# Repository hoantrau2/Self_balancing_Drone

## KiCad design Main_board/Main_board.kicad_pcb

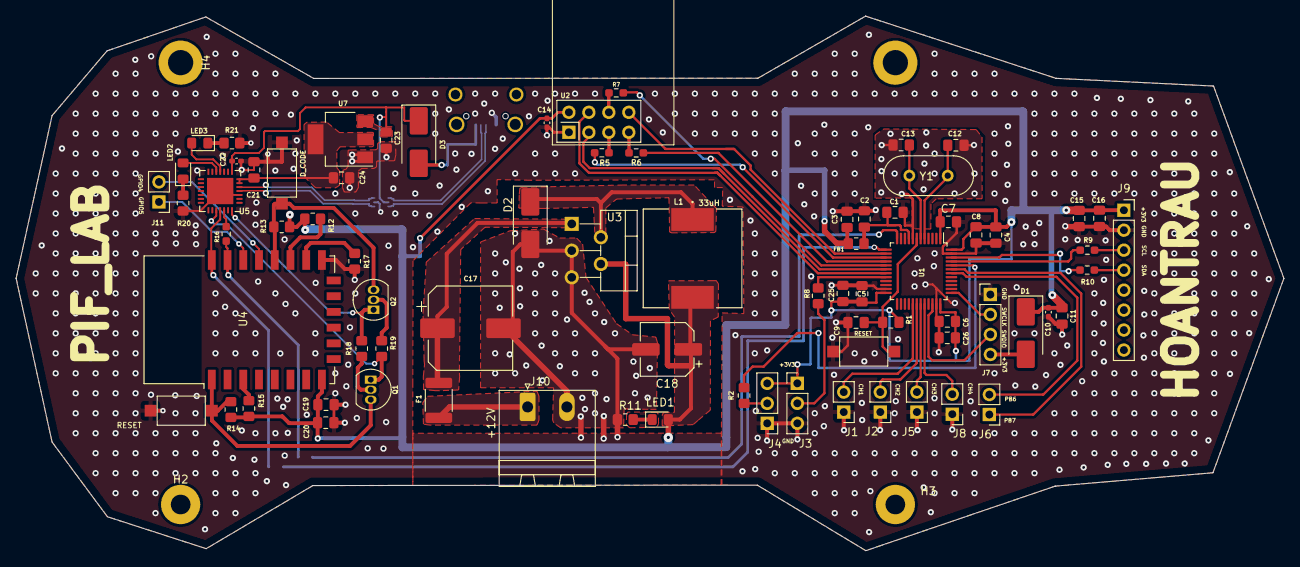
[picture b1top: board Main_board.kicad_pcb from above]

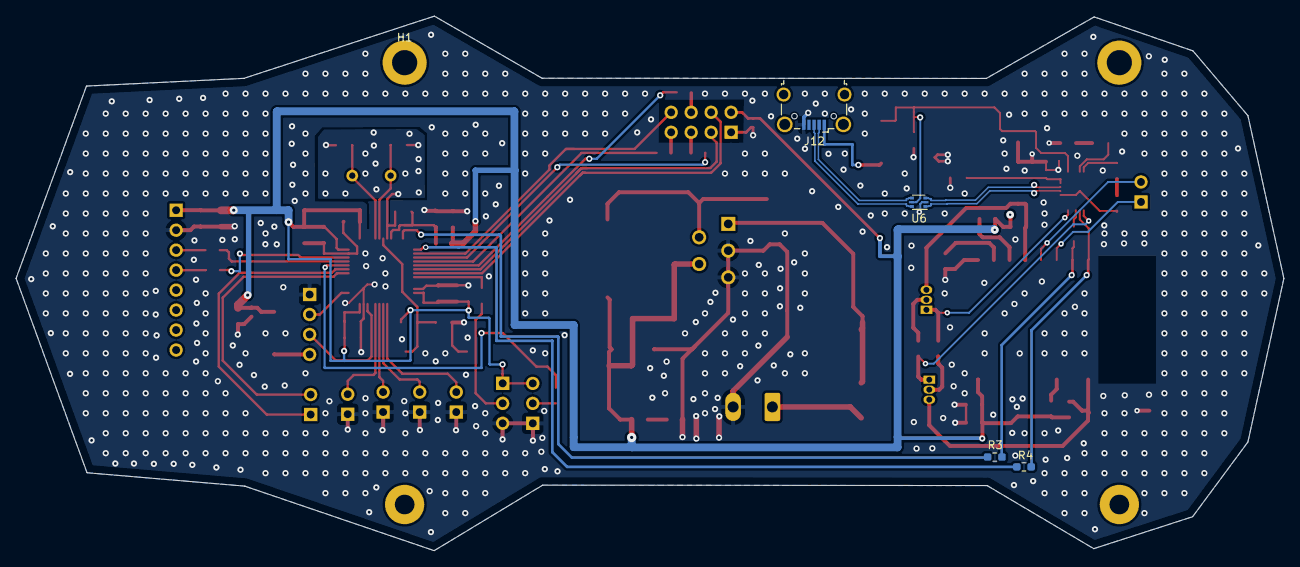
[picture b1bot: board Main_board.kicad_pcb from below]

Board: 2 copper layers, 161.2 x 68.0 mm, 85 parts (5 on the bottom side), 63 nets.

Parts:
C1: 10n; C_0805_2012Metric_Pad1.18x1.45mm_HandSolder
C2, C3: 1u; C_0805_2012Metric_Pad1.18x1.45mm_HandSolder
C4, C11, C15, C20, C23, C24, C25, C26: 10u; C_0805_2012Metric_Pad1.18x1.45mm_HandSolder
C5, C6, C7, C8, C19, C21: 100nF/50V; C_0805_2012Metric_Pad1.18x1.45mm_HandSolder
C9, C16: 100n; C_0805_2012Metric_Pad1.18x1.45mm_HandSolder
C10, C14, C22: 100nF/50V; C_0402_1005Metric_Pad0.74x0.62mm_HandSolder
C12, C13: 20p; C_0805_2012Metric_Pad1.18x1.45mm_HandSolder
C17: 680uF; CP_Elec_10x10.5
C18: 220uF; CP_Elec_6.3x7.7
D1, D2, D3: 1N5824; D_SMB_Handsoldering
D_CODE: BUTTON_GPIO0_ESP; SW_SPST_CK_RS282G05A3
F1: Fuse; Fuse_1812_4532Metric_Pad1.30x3.40mm_HandSolder
FB1: 120R; R_0805_2012Metric_Pad1.20x1.40mm_HandSolder
H1, H2, H3, H4: MountingHole; MountingHole_2.2mm_M2
J1, J2, J5, J6, J8, J11: Screw_Terminal_01x02; PinHeader_1x02_P2.54mm_Vertical
J3, J4: Screw_Terminal_01x03; PinHeader_1x03_P2.54mm_Vertical
J7: Conn_01x04_Pin; PinHeader_1x04_P2.54mm_Vertical
J9: MPU6050; PinSocket_1x08_P2.54mm_Vertical
J10: Screw_Terminal_01x02; PhoenixContact_MSTBA_2,5_2-G_1x02_P5.00mm_Horizontal
J12: USB_B_Micro; USB_Micro-B_Wuerth_629105150521_CircularHoles
L1: 33uH; IND_CDRH127_LDNP-470MC_SUM
LED1, LED2, LED3: LED; D_0805_2012Metric_Pad1.15x1.40mm_HandSolder
Q1, Q2: S8050; TO-92_Inline
R1: 10k; C_0805_2012Metric_Pad1.18x1.45mm_HandSolder
R2, R8, R13, R14, R15, R17: 10k; R_0805_2012Metric_Pad1.20x1.40mm_HandSolder
R3, R4, R5, R6, R7, R9, R10: 0; R_0603_1608Metric_Pad0.98x0.95mm_HandSolder
R11, R20, R21: 22; R_0805_2012Metric_Pad1.20x1.40mm_HandSolder
R12: 4k7; R_0805_2012Metric_Pad1.20x1.40mm_HandSolder
R16: 470; R_0603_1608Metric_Pad0.98x0.95mm_HandSolder
R18, R19: 12K; R_0805_2012Metric_Pad1.20x1.40mm_HandSolder
RESET: button_reset; SW_SPST_CK_RS282G05A3
RESET#2: Reset_button; SW_SPST_CK_RS282G05A3
U1: STM32F103C8T6; LQFP-48_7x7mm_P0.5mm
U2: NRF24L01_Breakout; nRF24L01_Breakout
U3: LM2596S-3.3; TO-220-5_P3.4x3.7mm_StaggerOdd_Lead3.8mm_Vertical
U4: ESP-12E
U5: CP2102N-Axx-xQFN28; QFN-28-1EP_5x5mm_P0.5mm_EP3.35x3.35mm
U6: USBLC6-2P6; SOT-666
U7: AMS1117-3.3; SOT-223-3_TabPin2
Y1: Crystal; Crystal_HC49-4H_Vertical

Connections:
3.3V_3A_OUT: C3.1, C4.1, C5.1, C6.1, C7.1, C8.1, C10.1, C11.1, C14.1, C15.1, C16.1, C18.1, C19.1, C20.1, C25.1, C26.1, D1.1 (K), FB1.2, J3.1, J4.3, J9.1, L1.2, LED1.2 (A), R1.1, R12.1, R13.1, R14.1, R15.1, U1.1 (VBAT), U1.24 (VDD), U1.36 (VDD), U1.48 (VDD), U2.2 (VCC), U3.4 (FB), U4.8 (VCC)
/BOOT1: J3.2, R8.1
/BOOTO: J4.2, R2.1
/ESP8266_12F/3V3_local: C21.1, C24.1, U5.6 (VDD), U5.7 (VREGIN), U7.2 (VO)
/ESP8266_12F/5V_local: C22.1, C23.1, D3.1 (K), U5.8 (VBUS), U6.5 (VBUS), U7.3 (VI)
/ESP8266_12F/DTR: Q2.1 (E), R18.2, U5.28 (~DTR)
/ESP8266_12F/GPIO0: D_CODE.1, Q2.3 (C), R13.2, U4.18 (GPIO0)
/ESP8266_12F/RST_ESP: Q1.3 (C), R14.2, RESET.2, U4.1 (~RST)
/ESP8266_12F/RTS: Q1.1 (E), R19.2, U5.24 (~RTS)
/ESP8266_12F/USB_COM_D+: J12.3 (D+), U6.6 (I/O1)
/ESP8266_12F/USB_COM_D-: J12.2 (D-), U6.4 (I/O2)
/ESP8266_12F/USB_D+: U5.4 (D+), U6.1 (I/O1)
/ESP8266_12F/USB_D-: U5.5 (D-), U6.3 (I/O2)
/ESP8266_12F/VBUS_USB: D3.2 (A), J12.1 (VBUS)
/HSE_IN: C12.2, U1.5 (PD0), Y1.1
/HSE_OUT: C13.2, U1.6 (PD1), Y1.2
/N_RESET: C9.1, R1.2, RESET#2.2, U1.7 (NRST)
/SWCLK: J7.2, U1.37 (PA14)
/SWDIO: J7.3, U1.34 (PA13)
/power/12V_INPUT: F1.1, J10.1
/power/LMS_Vin: C17.1, F1.2, U3.1 (VIN)
/power/diode: D2.1 (K), L1.1, U3.2 (OUT)
GND: C1.2, C2.2, C3.2, C4.2, C5.2, C6.2, C7.2, C8.2, C9.2, C10.2, C11.2, C12.1, C13.1, C14.2, C15.2, C16.2, C17.2, C18.2, C19.2, C20.2, C21.2, C22.2, C23.2, C24.2, C25.2, C26.2, D2.2 (A), D_CODE.2, J1.1, J2.1, J3.3, J4.1, J5.1, J7.1, J8.1, J9.2, J10.2, J12.5 (GND), R11.2, R17.2, R20.2, R21.2, RESET.1, RESET#2.1, U1.8 (VSSA), U1.23 (VSS), U1.35 (VSS), U1.47 (VSS), U2.1 (GND), U3.3 (GND), U3.5 (~ON/OFF), U4.15 (GND), U5.3 (GND), U5.29 (GND), U6.2 (GND), U7.1 (GND)
GPIO4_ESP: J11.2, U4.19 (GPIO4)
GPIO5_ESP: J11.1, U4.20 (GPIO5)
NRF_CE: U1.18 (PB0), U2.3 (CE)
NRF_CSN: U1.19 (PB1), U2.4 (~CSN)
NRF_IRQ: U1.14 (PA4), U2.8 (IRQ)
NRF_MISO: R6.1, U2.7 (MISO)
NRF_MOSI: R7.1, U2.6 (MOSI)
NRF_SCK: R5.1, U2.5 (SCK)
unnamed: D1.2 (A), J7.4
unnamed: J6.1, U1.43 (PB7)
unnamed: J6.2, U1.42 (PB6)
unnamed: LED1.1 (K), R11.1
unnamed: LED2.2 (A), U5.12 (SUSPEND)
unnamed: LED2.1 (K), R20.1
unnamed: LED3.2 (A), U5.11 (~SUSPEND)
unnamed: LED3.1 (K), R21.1
unnamed: Q1.2 (B), R18.1
unnamed: Q2.2 (B), R19.1
unnamed: R2.2, U1.44 (BOOT0)
unnamed: R3.1, U1.12 (PA2)
unnamed: R4.1, U1.13 (PA3)
unnamed: R5.2, U1.15 (PA5)
unnamed: R6.2, U1.16 (PA6)
unnamed: R7.2, U1.17 (PA7)
unnamed: R8.2, U1.20 (PB2)
unnamed: R9.2, U1.45 (PB8)
unnamed: R10.2, U1.46 (PB9)
unnamed: C1.1, C2.1, FB1.1, U1.9 (VDDA)
unnamed: R15.2, U4.3 (EN)
unnamed: R12.2, U4.17 (GPIO2)
unnamed: R17.1, U4.16 (GPIO15)
unnamed: R16.2, U5.26 (TXD)
RXD_ESP: R3.2, R16.1, U4.21 (GPIO3/RXD)
SCL_MPU: J9.3, R9.1
SDA_MPU: J9.4, R10.1
TIM1_CH1: J1.2, U1.29 (PA8)
TIM1_CH2: J2.2, U1.30 (PA9)
TIM1_CH3: J5.2, U1.31 (PA10)
TIM1_CH4: J8.2, U1.32 (PA11)
TXD_ESP: R4.2, U4.22 (GPIO1/TXD), U5.25 (RXD)

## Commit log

2023-09-22 Start the project by designing the PCB main board using KiCad.
